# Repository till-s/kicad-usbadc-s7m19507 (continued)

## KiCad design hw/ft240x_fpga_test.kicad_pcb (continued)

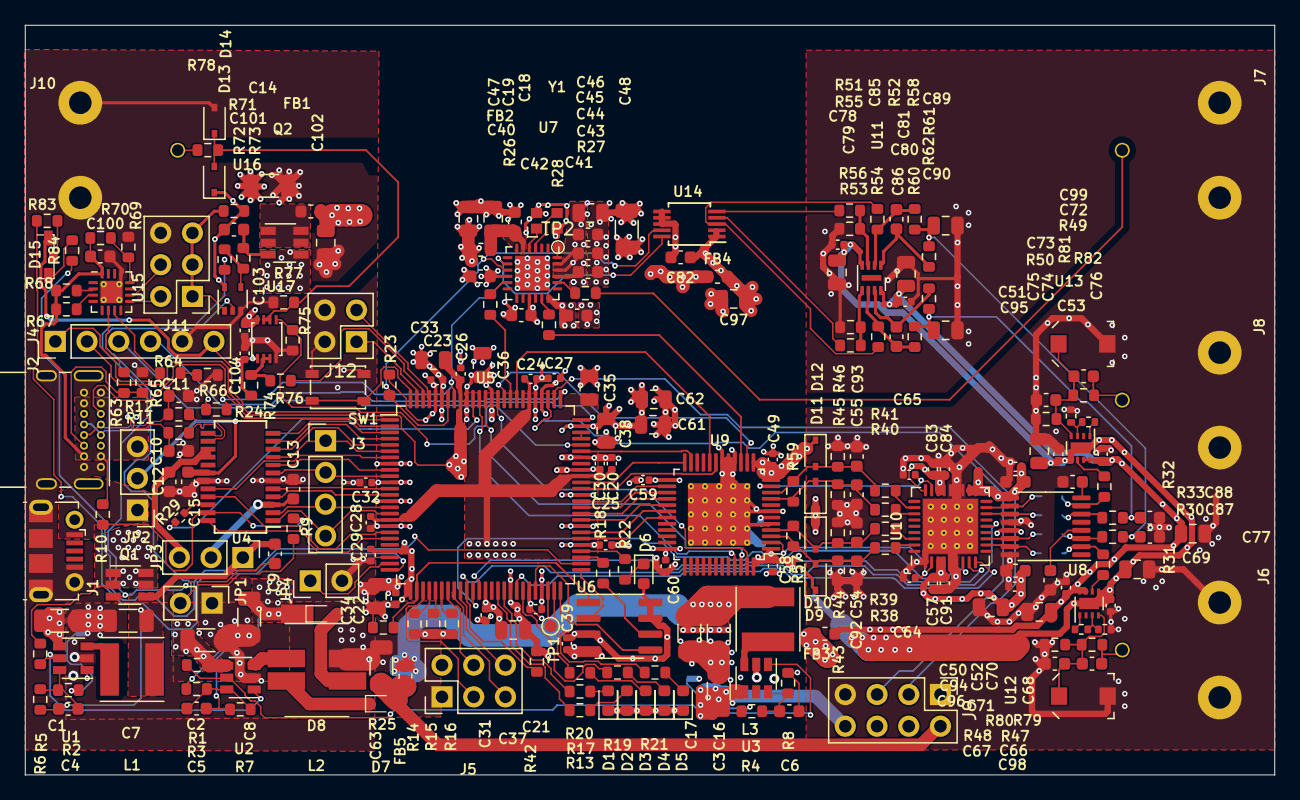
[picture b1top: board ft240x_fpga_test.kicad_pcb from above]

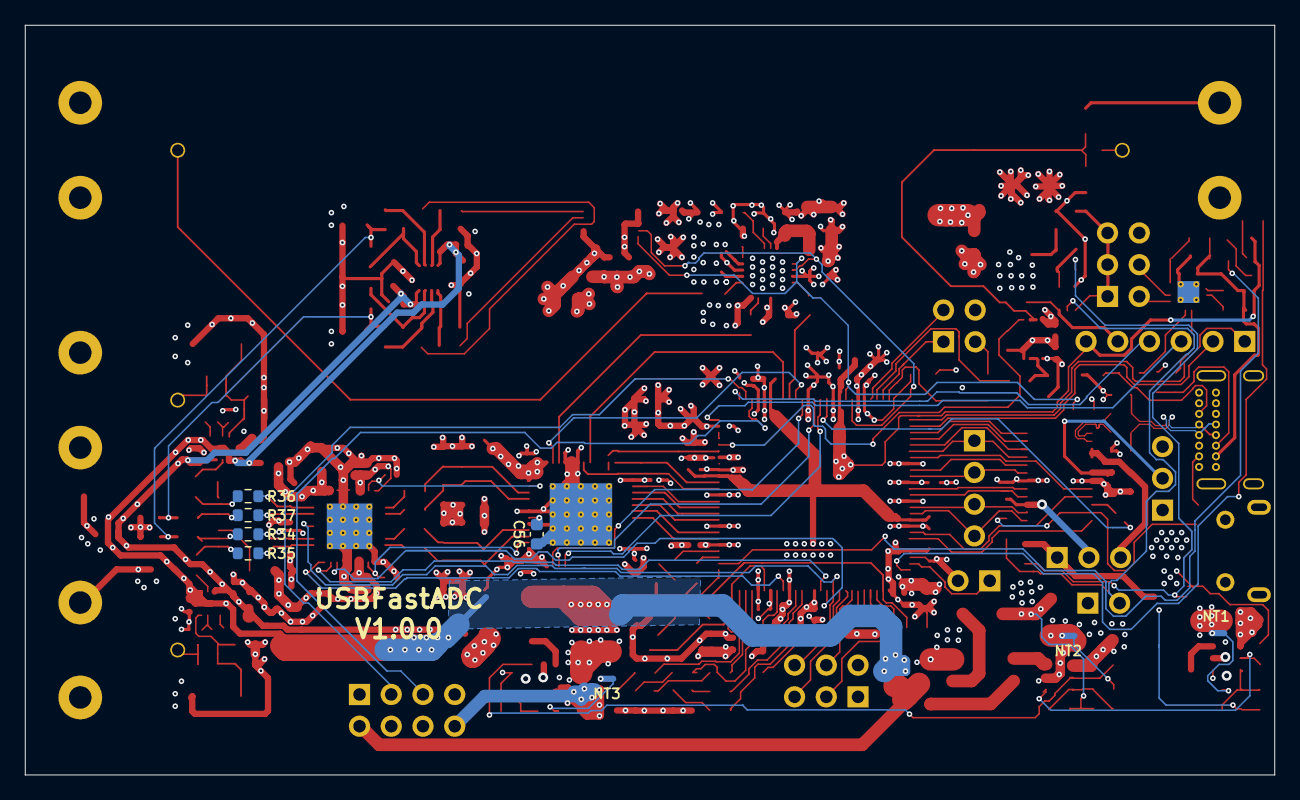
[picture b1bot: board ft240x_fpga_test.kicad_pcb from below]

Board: 4 copper layers, 100.0 x 60.0 mm, 253 parts (8 on the bottom side), 180 nets.

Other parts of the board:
D15: LED_Front; LED_Wuerth_Sideview
J12: PUDC_B/IN; PinHeader_2x02_P2.54mm_Vertical
R78: 50; R_0603_1608Metric
R83, R84: 1k5; R_0603_1608Metric
TP2: Ref; TestPoint_Pad_D0.8mm_no_CY

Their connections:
+2V5: D15.2; also elsewhere on the board
/fpga_xc3s/LED_FRONT_G: R84.1; also elsewhere on the board
/fpga_xc3s/sheet60F7998F/DIGIO: R78.1; also elsewhere on the board
unnamed: D15.1, R83.2
unnamed: D15.3, R84.2
unnamed 158: R83.1; also elsewhere on the board
unnamed 161: TP2.1; also elsewhere on the board

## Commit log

2021-05-13 git import
2021-05-13 added missing schematic files
2021-05-13 .gitignore: ignore .xml file; seems to be generated by BOM
2021-06-04 several updates...
2021-06-04 Started to work on analog front-end; ADC connected to fpga
2021-06-08 added buffer amps for offset dac
2021-07-01 more work (don't recall details :-()
2021-07-19 everything hooked up + layed out; 0.2/0.4mm vias :-(
2021-07-19 pcb: increased min. via dia to 0.45mm (jlcpcb)
2021-07-20 prototype version
2021-07-20 changed options for gerber (according to jlcpcb instructions)
2021-07-20 updated gerber options according to jlcpcb instructions
2021-08-29 started git control
2021-08-30 top: hooked up FIFO block -- LEDs do not work anymore ?!
2021-08-30 led only
2021-08-30 restored constraints after 'back-annotating' messed it up...
2021-08-31 Implemented bit-banging
2021-09-01 BUGFIX: bit-bang interface
    would keep receiving from the fifo even if the TX fifo
    was full; losing transactions.
    Moved the bit-bang IF to a dedicated VHD module.
2021-09-01 removed debugging code (installed to debug bit-bang IF)
2021-09-12 top.vhd/ucf: connected IO connector, new CommandWrapper; timing constraints
    added period constraint for adc clock. For now the pll clock is used to
    clock the block ram writing (testing).
2021-09-12 added ISE tcl file to git
2021-10-25 updated bit-bang interface; added CSb mux for ADC and PGA SPIs
2021-10-25 Add ILAWrapperPkg.vhd to TCL script
2021-10-25 top.vhd: converted 'case' to 'if' (silence ise warnings about non locally constant items)
2021-10-28 Debugged ADC interface; seems to work now
2021-10-29 connected front LED
2021-11-04 added 'usb-support' as a submodule; updated TCL script
2021-11-04 added makefile for creating git version package
2021-11-14 Hooked up WordSpiIF for first testing
2021-11-14 top.vhd: connected some more SPI signals to SPI ILA
2021-11-14 testing dedicated SPI master -> no significant improvement of programming speed
2021-11-14 removed dedicated SPI controller again (no improvement of programming speed)
2021-11-14 Reverted dedicated SPI - some fixed
    - removed SPI controller from TCL
    - had used the wrong submodule branch (still including the SPI)
2021-11-14 Removed more left-overs from dedicated-SPI test
2021-11-14 submodule update
2021-12-04 passed mapping with decimators
2021-12-05 further testing of submodule; saving some slices
    -> got it mapped and pass timing
2021-12-10 increased memory size to max supported by 200 device
2021-12-10 xc3s-test.tcl: updated project settings; use only values differing from default
2021-12-10 xc3s-test.tcl: must execute set_process_properties when recreating project
    Otherwise all the settings are not used, of course.
2021-12-10 submodule update: MSIZE command flushes the read buffer
2021-12-10 submodule update: DISABLE_DECIMATORS_G generic now available in wrapper
2021-12-10 top.vhd: use DEVICE_G generic to disable features when built for xc3s50a
2021-12-10 top.vhd: fixed typos; added .gitignore (GitVersionPkg.vhd)
2021-12-10 submodule update: DPRAM readout fix; switched back to dual mem anyways
2021-12-23 submodule update; fixed auto-timer (wouldn't work with decimation)
2021-12-23 submodule update (timing fix)
2021-12-23 submodule update (don't flush read buffer when querying memory depth)
2021-12-24 submodule update: fix in computation of scale/shift for cic1
2022-01-30 ICAP rework
2022-01-30 multiboot image for xc3s50a
    Embed multiboot address as constant so it is logged in git.
    Use ICAP when the multiboot address is /= 0 and boot the next
    image when the jumper is off.
2022-01-30 top.vhd: non-multiboot image
2022-01-30 submodule update (software)
2022-01-30 fallback-version (with icap multiboot enabled)
2022-01-30 top.vhd: fixed typo
2022-01-30 disabled ICAP ('normal' image)
2022-01-30 top.vhd: disable ICAP_ILA (target is the xc3s200 with decimator filters)
2022-02-07 Connected a (internal) SPI register to control the front-end gain
2022-02-07 top.vhd: support read-only access to FEG register (use hi-z bit as r/w flag)
2022-02-08 top.vhd: hooked up FEG control bits (BROKEN?); disabled ICAP
    Something seems broken; image doesn't boot :-(
2022-02-08 submodule update: BitBang/SpiReg fixes
2022-02-08 top.vhd: check DEVICE_G against supported device names
2022-02-08 .gitignore: added 'image' directory, fixed version package file name
2022-02-08 submodule update (sw updates)
2022-02-08 project TCL: disable setting multiboot parameters in bitstream;
    By default bitgen always sets the multiboot parameters. We want
    to disable so the image can use the info in the GENERAL registers
    to determine where it was booted from.
    Unfortunately, setting the "Other Bitgen Command Line Options"
    property does not make it from TCL into the project file.
    Luckily I found a work-around (reopen project from TCL, set
2022-03-26 top.vhd: fixed IO_DAT hookup; was on IO_L06_P_1 instead of IO_L06_P_0
2022-03-26 submodule update: improved CIC0 scaling
2022-03-26 usbadc-support: submod update; reduced RAM_BITS to 8
2022-03-26 top.vhd: use constant to define ADC bit width
2023-04-20 submodule update: SW fix.
2023-06-30 submodule update (GUI)
